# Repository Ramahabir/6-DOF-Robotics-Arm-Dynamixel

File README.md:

# STM32F411 6-DOF Robot Arm Controller

Firmware for a 6-degree-of-freedom robot arm based on an STM32F411CEU6 (Black Pill). The controller operates four Dynamixel joints over a half-duplex serial bus and provides PWM channels for the end effector.

The project uses STM32Cube HAL with PlatformIO and is uploaded through the USB-to-TTL serial adapter (upload protocol `serial`).

## System overview

- **4 × Dynamixel joints** — controlled through USART2 using Dynamixel Protocol 1.0
- **1 × wrist/gripper rotation servo** — PWM output on PA8 (TIM1_CH1, configured but not started)
- **1 × gripper servo** — PWM output on PA6 (TIM3_CH1)
- **USB-to-TTL data logger/telemetry** — connected through USART1 (PB6/PB7)
- **ESP32-C3 Super Mini** — planned wireless interface through USART6 (PA11/PA12)
- **74LS241 buffer** — converts the Dynamixel UART connection into a controlled half-duplex bus

## Hardware

- STM32F411CEU6 Black Pill development board
- Dynamixel AX-series actuators (the driver currently targets the AX-12A control table)
- 74LS241 tri-state buffer for the Dynamixel half-duplex bus
- Two PWM-compatible hobby servos
- USB-to-TTL serial adapter
- ESP32-C3 Super Mini (planned)
- Suitable external power supplies for the Dynamixel and hobby servos

## Controller PCB

The repository includes the editable KiCad source for the custom controller PCB. The board combines the STM32F411 Black Pill, ESP32-C3 Super Mini, 74LS241 Dynamixel interface, power input, actuator connectors, and development headers on one carrier board.

Open [`pcb/6dof.kicad_pro`](pcb/6dof.kicad_pro) in **KiCad 9.0 or newer** to view or modify the complete project.

### Schematic

Editable source: [`pcb/6dof.kicad_sch`](pcb/6dof.kicad_sch)

### PCB layout

Editable source: [`pcb/6dof.kicad_pcb`](pcb/6dof.kicad_pcb)

### 3D preview

> The KiCad files are active design sources. Review the schematic, complete the design-rule checks, and verify all footprints and routing before ordering a PCB. Gerber files, drill files, and a bill of materials are not included yet.

## Pin assignment

| Function | STM32 peripheral | Pin | Direction | Notes |
|---|---|---:|---|---|
| Dynamixel TX | USART2_TX | PA2 | Output | 1 Mbps, 8-N-1 |
| Dynamixel RX | USART2_RX | PA3 | Input | Receives Dynamixel status packets |
| 74LS241 direction | GPIO | PB0 | Output | High = transmit, low = receive/bus released |
| Data logger/telemetry TX | USART1_TX | PB6 | Output | 115200, 8-N-1; connect to USB-to-TTL RX |
| Data logger RX | USART1_RX | PB7 | Input | Connect to USB-to-TTL TX |
| ESP32-C3 TX | USART6_TX | PA11 | Output | 115200, 8-N-1; planned wireless link; connect to ESP32 RX |
| ESP32-C3 RX | USART6_RX | PA12 | Input | Planned wireless link; connect to ESP32 TX |
| Gripper rotation servo | TIM1_CH1 | PA8 | PWM output | Rotates the gripper (not started by default) |
| Gripper servo | TIM3_CH1 | PA6 | PWM output | Opens and closes the gripper |
| Built-in status LED | GPIO | PC13 | Output | Active-low on the Black Pill |

> The README pin table matches the generated firmware. If you target the earlier `PA9/PA10` USART1 design, update the alternate-function configuration in `src/usart.c` before wiring.

## Dynamixel bus

Dynamixel Protocol 1.0 uses a single bidirectional data wire. USART2 provides separate TX and RX signals, so the 74LS241 is used to control when the STM32 drives the bus.

```text
STM32 PA2 (USART2_TX) ──> 74LS241 input
STM32 PB0 (DIR)       ──> 74LS241 output-enable/direction control
74LS241 bus output    ──> Dynamixel DATA
STM32 PA3 (USART2_RX) <── Dynamixel DATA / receive path

STM32 GND ─────────────── Dynamixel interface GND
```

The firmware sets PB0 high while transmitting and returns it low before waiting for a servo response. USART2 is configured for **1,000,000 baud, 8 data bits, no parity, and 1 stop bit**.

Do not power the actuators from the STM32 board. Use correctly rated external supplies and connect the grounds of the STM32, servo supplies, Dynamixel bus, USB-to-TTL adapter, and ESP32 interface.

## Joint IDs

The current firmware polls the following joints. With torque off, move them by hand and verify the reported raw values change.

| Joint | Dynamixel ID | Notes |
|---|---:|---|
| Base | 1 | Home ≈ 512 |
| Shoulder | 9 | Home ≈ 315 |
| Elbow | 13 | Home ≈ 512 |
| Wrist | 3 | Home ≈ 512 |

For AX-series position control, raw values `0..1023` represent approximately `0..300°`:

```text
angle = raw_position × 300 / 1023
```

## Telemetry output

The firmware runs with **torque off** on all four joints. It reads present position, speed, load, voltage, temperature, and the moving flag for each joint, then prints one line to **both USART1 and USART6** (115200 baud, 8-N-1):

```text
BASE,826,0,0,124,32,IDL SHD,651,0,0,121,32,IDL ELB,557,0,0,124,32,IDL WRI,532,0,0,124,32,IDL
```

Each joint is separated by a space and contains comma-separated fields:

| Field | Meaning |
|---|---|
| `NAME` | Joint name (`BASE`, `SHD`, `ELB`, `WRI`) |
| `pos` | Present position, raw 0–1023 |
| `spd` | Present speed (0–1023); 0 = stationary |
| `load` | Present load, centered on 0 |
| `V` | Supply voltage in tenths of a volt (e.g. `124` = 12.4 V) |
| `T` | Servo board temperature in °C |
| `mov` | `IDL` = idle, `MOV` = rotating |

If a joint does not respond, that joint prints `NAME,ERROR,<code>` instead of numeric fields. On startup, USART1 also prints `Dynamixel ready (torque off)` once.

## Firmware status

Currently implemented:

- USART2 Dynamixel Protocol 1.0 communication at 1 Mbps, half-duplex direction control through PB0
- Ping, 8/16-bit read and write, torque, LED, goal-position, speed, present-position, present-speed, load, voltage, temperature, and moving-flag commands
- Packet validation for ID, length, checksum, timeout, and servo-reported errors
- Telemetry logging to USART1 (PB6/PB7) and USART6 (PA11/PA12) at 115200 baud
- Torque-off startup so joints can be moved by hand while powered
- TIM3 channel 1 PWM for PA6 (started); TIM1 channel 1 PWM for PA8 (configured, not started)

Still to be integrated into the active application:

- Enable torque and add coordinated motion control for the arm axes
- Start the TIM1 (PA8) gripper-rotation PWM channel
- Define the command protocol between the STM32 and ESP32-C3
- Optional data-fusion/feedback layer for closed-loop control

## Building and uploading

### Requirements

- [Visual Studio Code](https://code.visualstudio.com/) with the PlatformIO extension, or PlatformIO Core
- USB-to-TTL serial adapter
- External power supplies for the Dynamixel actuators

### PlatformIO commands

Build the firmware:

```sh
pio run
```

Upload over the serial adapter (the default `upload_protocol = serial` must match the connected adapter and bootloader):

```sh
pio run --target upload
```

Open the serial monitor on the USB-to-TTL adapter (e.g. `COM11`) for telemetry output:

```sh
pio device monitor --port COM11 --baud 115200
```

The PlatformIO environment is `genericSTM32F411CE`, using the STM32Cube framework and serial upload.

## Project structure

```text
.
├── include/
│   ├── dynamixel.h       # Dynamixel driver API and control-table addresses
│   ├── gpio.h
│   ├── main.h
│   ├── tim.h
│   └── usart.h
├── docs/
│   ├── 3dpcb.png         # Render of the assembled controller PCB
│   ├── pcb_footprint.png # PCB routing and footprint preview
│   ├── schematic.png     # Controller schematic preview
│   └── stm32pinout.png   # STM32 peripheral pin assignment
├── pcb/
│   ├── 6dof.kicad_pcb    # Editable PCB layout
│   ├── 6dof.kicad_pro    # KiCad project settings
│   └── 6dof.kicad_sch    # Editable schematic
├── src/
│   ├── dynamixel.c       # Protocol 1.0 packet transport and commands
│   ├── gpio.c            # LED and 74LS241 direction GPIO setup
│   ├── main.c            # Active test application
│   ├── tim.c             # PA8 and PA6 PWM timer configuration
│   └── usart.c           # USART1 and USART2 configuration
├── main_lama/            # Earlier application code kept for reference
└── platformio.ini        # PlatformIO target and build configuration
```

## Safety notes

- Test one actuator at a time before operating the complete arm.
- Verify Dynamixel IDs and baud rates before enabling torque.
- Keep the arm clear of people and objects during first motion tests.
- Use a current-limited actuator supply and provide an accessible emergency power cutoff.
- Set conservative position and speed limits in software to prevent mechanical collisions.
- Never connect 5 V logic directly to a non-5-V-tolerant STM32 input; verify the complete 74LS241 interface and supply arrangement before powering it.

## License

This project is open-source software available under the [MIT License](LICENSE).

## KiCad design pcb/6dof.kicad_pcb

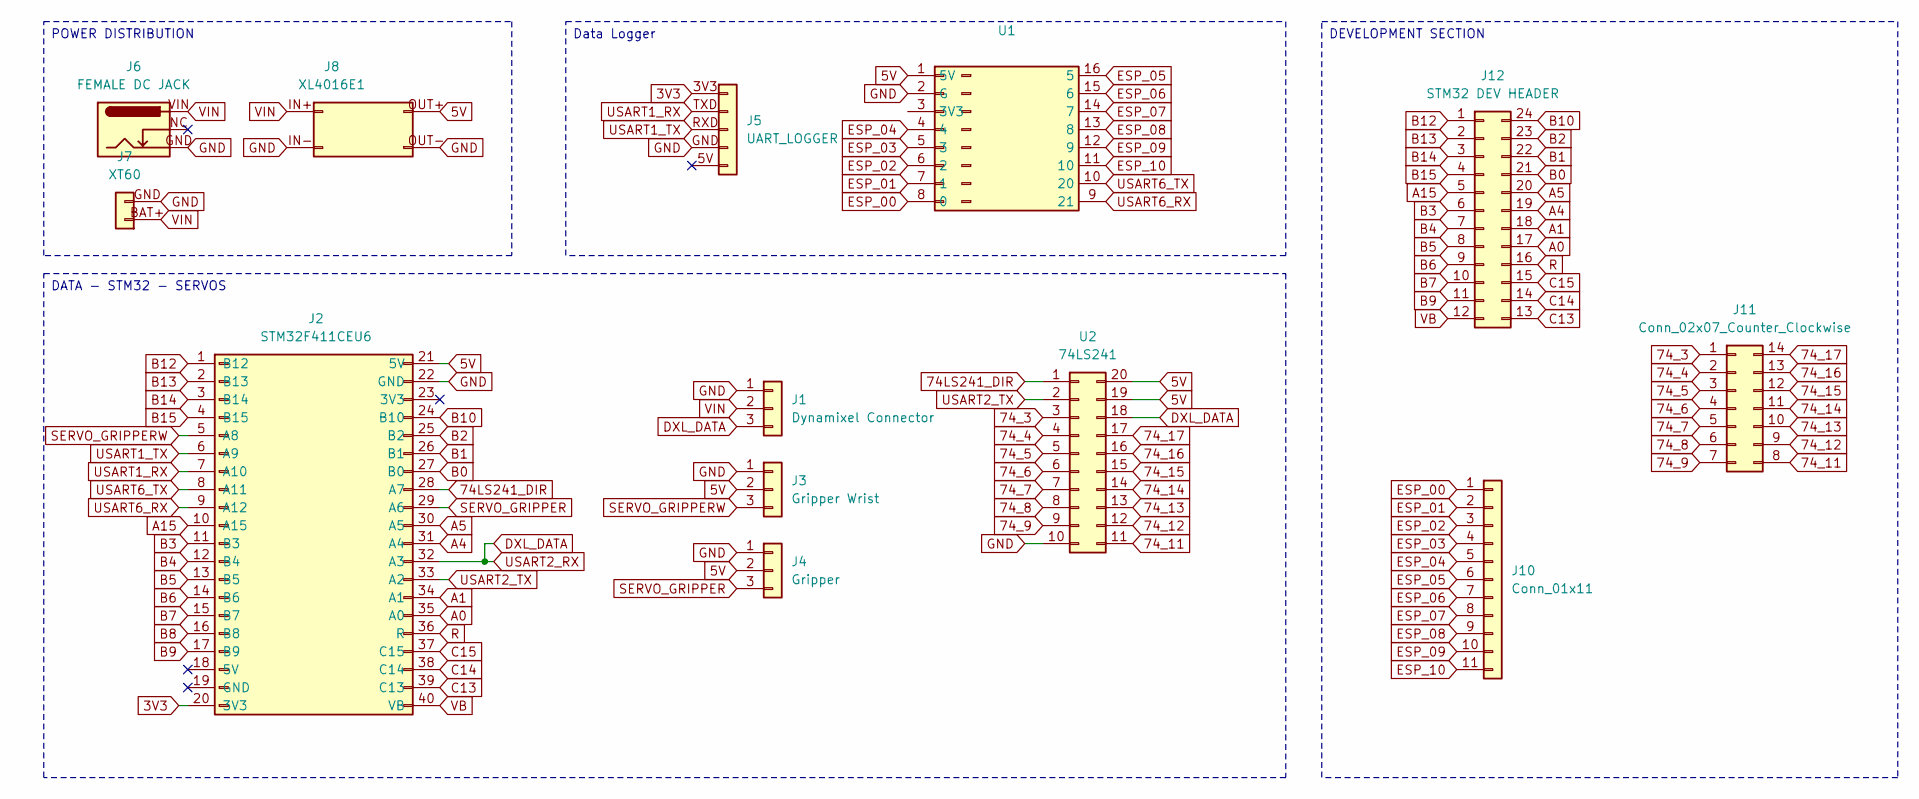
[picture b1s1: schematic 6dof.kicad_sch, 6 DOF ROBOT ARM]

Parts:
J1: Dynamixel Connector; Molex_KK-254_AE-6410-03A_1x03_P2.54mm_Vertical
J2: STM32F411CEU6
J3: Gripper Wrist; Molex_KK-254_AE-6410-03A_1x03_P2.54mm_Vertical
J4: Gripper; Molex_KK-254_AE-6410-03A_1x03_P2.54mm_Vertical
J5: UART_LOGGER; Molex_KK-254_AE-6410-05A_1x05_P2.54mm_Vertical
J6: FEMALE DC JACK; BarrelJack_CUI_PJ-102AH_Horizontal
J7: XT60; AMASS_XT60PW-M_1x02_P7.20mm_Horizontal
J8: XL4016E1
J10: Conn_01x11; PinHeader_1x11_P2.54mm_Vertical
J11: Conn_02x07_Counter_Clockwise; PinHeader_2x07_P2.54mm_Vertical
J12: STM32 DEV HEADER; PinHeader_2x12_P2.54mm_Vertical
U1: ESP32 C3 SUPERMINI
U2: 74LS241; DIP-20_W7.62mm

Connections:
3V3: J2.20 (3V3), J5.3V3
5V: J2.21 (5V), J3.2, J4.2, J8.OUT+ (Pin_4), U1.1 (5V), U2.19, U2.20
74LS241_DIR: J2.28 (A7), U2.1
74_3: J11.1, U2.3
74_4: J11.2, U2.4
74_5: J11.3, U2.5
74_6: J11.4, U2.6
74_7: J11.5, U2.7
74_8: J11.6, U2.8
74_9: J11.7, U2.9
74_11: J11.8, U2.11
74_12: J11.9, U2.12
74_13: J11.10, U2.13
74_14: J11.11, U2.14
74_15: J11.12, U2.15
74_16: J11.13, U2.16
74_17: J11.14, U2.17
A0: J2.35 (A0), J12.17
A1: J2.34 (A1), J12.18
A4: J2.31 (A4), J12.19
A5: J2.30 (A5), J12.20
A15: J2.10 (A15), J12.5
B0: J2.27 (B0), J12.21
B1: J2.26 (B1), J12.22
B2: J2.25 (B2), J12.23
B3: J2.11 (B3), J12.6
B4: J2.12 (B4), J12.7
B5: J2.13 (B5), J12.8
B6: J2.14 (B6), J12.9
B7: J2.15 (B7), J12.10
B8: J2.16 (B8)
B9: J2.17 (B9), J12.11
B10: J2.24 (B10), J12.24
B12: J2.1 (B12), J12.1
B13: J2.2 (B13), J12.2
B14: J2.3 (B14), J12.3
B15: J2.4 (B15), J12.4
C13: J2.39 (C13), J12.13
C14: J2.38 (C14), J12.14
C15: J2.37 (C15), J12.15
DXL_DATA: J1.3, J2.32 (A3), U2.18
ESP_00: J10.1, U1.8 (0)
ESP_01: J10.2, U1.7 (1)
ESP_02: J10.3, U1.6 (2)
ESP_03: J10.4, U1.5 (3)
ESP_04: J10.5, U1.4
ESP_05: J10.6, U1.16 (5)
ESP_06: J10.7, U1.15 (6)
ESP_07: J10.8, U1.14 (7)
ESP_08: J10.9, U1.13 (8)
ESP_09: J10.10, U1.12 (9)
ESP_10: J10.11, U1.11 (10)
GND: J1.1, J2.22 (GND), J3.1, J4.1, J5.GND, J6.GND, J7.GND (Pin_2), J8.IN- (Pin_2), J8.OUT- (Pin_3), U1.2 (G), U2.10
R: J2.36 (R), J12.16
SERVO_GRIPPER: J2.29 (A6), J4.3
SERVO_GRIPPERW: J2.5 (A8), J3.3
USART1_RX: J2.7 (A10), J5.TXD
USART1_TX: J2.6 (A9), J5.RXD
USART2_TX: J2.33 (A2), U2.2
USART6_RX: J2.9 (A12), U1.9 (21)
USART6_TX: J2.8 (A11), U1.10 (20)
VB: J2.40 (VB), J12.12
VIN: J1.2, J6.VIN, J7.BAT+ (Pin_1), J8.IN+ (Pin_1)

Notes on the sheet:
DATA - STM32 - SERVOS
DEVELOPMENT SECTION
Data Logger
POWER DISTRIBUTION

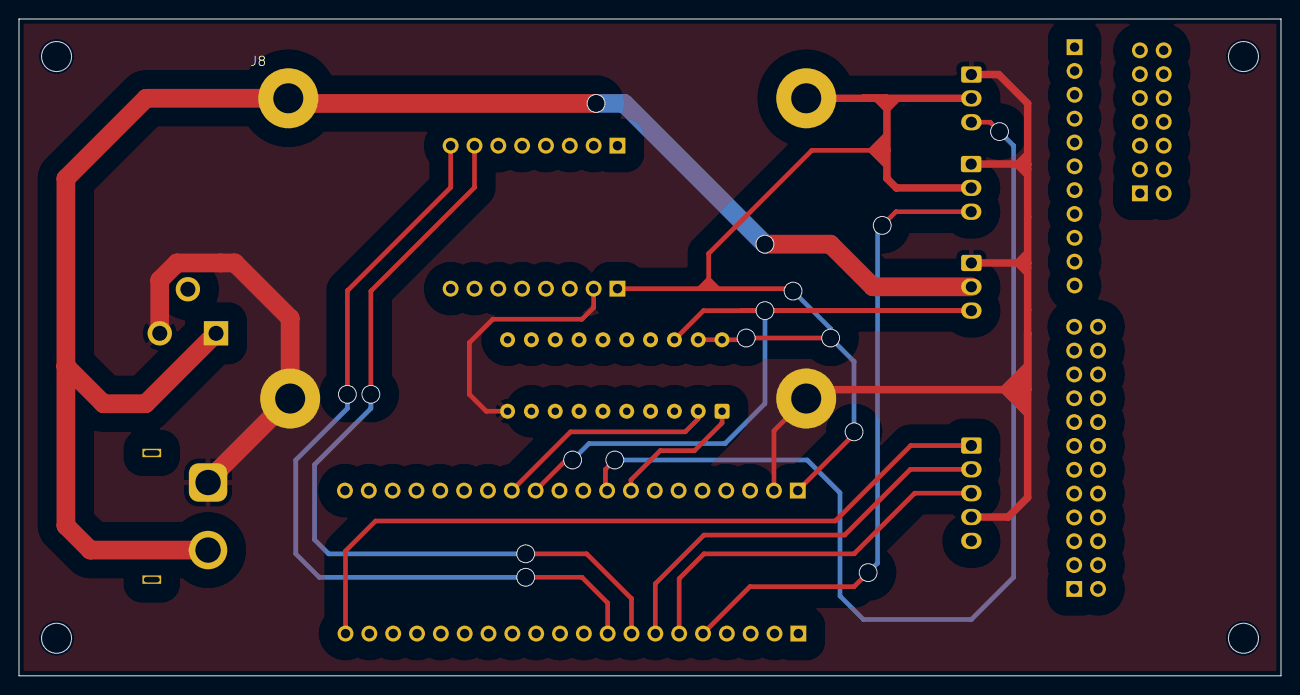
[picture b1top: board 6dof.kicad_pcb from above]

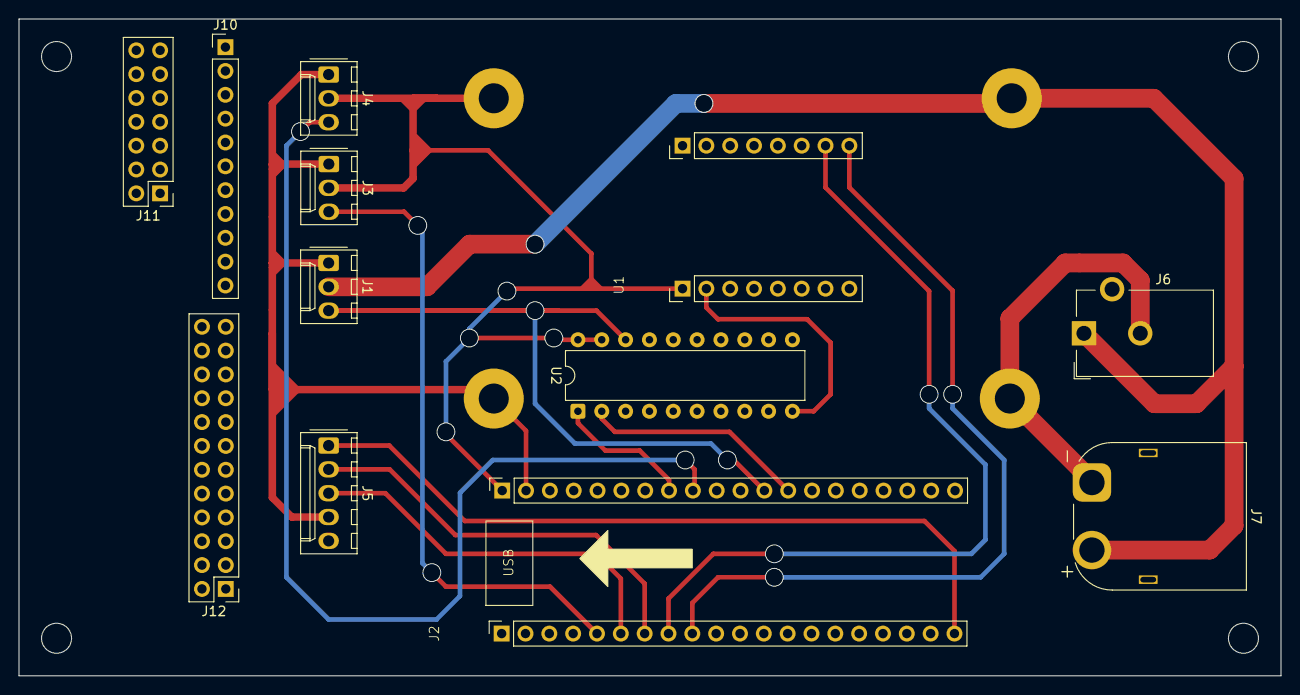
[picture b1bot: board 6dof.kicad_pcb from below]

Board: 2 copper layers, 134.5 x 70.0 mm, 13 parts (12 on the bottom side), 62 nets.

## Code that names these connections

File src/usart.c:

/* USER CODE BEGIN Header */
/**
  ******************************************************************************
  * @file    usart.c
  * @brief   This file provides code for the configuration
  *          of the USART instances.
  ******************************************************************************
  * @attention
  *
  * Copyright (c) 2026 STMicroelectronics.
  * All rights reserved.
  *
  * This software is licensed under terms that can be found in the LICENSE file
  * in the root directory of this software component.
  * If no LICENSE file comes with this software, it is provided AS-IS.
  *
  ******************************************************************************
  */
/* USER CODE END Header */
/* Includes ------------------------------------------------------------------*/
#include "usart.h"

/* USER CODE BEGIN 0 */

/* USER CODE END 0 */

UART_HandleTypeDef huart1;
UART_HandleTypeDef huart2;
UART_HandleTypeDef huart6;

/* USART1 init function */

void MX_USART1_UART_Init(void)
{

  /* USER CODE BEGIN USART1_Init 0 */

  /* USER CODE END USART1_Init 0 */

  /* USER CODE BEGIN USART1_Init 1 */

  /* USER CODE END USART1_Init 1 */
  huart1.Instance = USART1;
  huart1.Init.BaudRate = 115200;
  huart1.Init.WordLength = UART_WORDLENGTH_8B;
  huart1.Init.StopBits = UART_STOPBITS_1;
  huart1.Init.Parity = UART_PARITY_NONE;
  huart1.Init.Mode = UART_MODE_TX_RX;
  huart1.Init.HwFlowCtl = UART_HWCONTROL_NONE;
  huart1.Init.OverSampling = UART_OVERSAMPLING_16;
  if (HAL_UART_Init(&huart1) != HAL_OK)
  {
    Error_Handler();
  }
  /* USER CODE BEGIN USART1_Init 2 */

  /* USER CODE END USART1_Init 2 */

}
/* USART2 init function */

void MX_USART2_UART_Init(void)
{

  /* USER CODE BEGIN USART2_Init 0 */

  /* USER CODE END USART2_Init 0 */

  /* USER CODE BEGIN USART2_Init 1 */

  /* USER CODE END USART2_Init 1 */
  huart2.Instance = USART2;
  /* AX-series factory-default bus speed. */
  huart2.Init.BaudRate = 1000000;
  huart2.Init.WordLength = UART_WORDLENGTH_8B;
  huart2.Init.StopBits = UART_STOPBITS_1;
  huart2.Init.Parity = UART_PARITY_NONE;
  huart2.Init.Mode = UART_MODE_TX_RX;
  huart2.Init.HwFlowCtl = UART_HWCONTROL_NONE;
  huart2.Init.OverSampling = UART_OVERSAMPLING_16;
  if (HAL_UART_Init(&huart2) != HAL_OK)
  {
    Error_Handler();
  }
  /* USER CODE BEGIN USART2_Init 2 */

  /* USER CODE END USART2_Init 2 */

}

/* USART6 init function */

void MX_USART6_UART_Init(void)
{
  huart6.Instance = USART6;
  huart6.Init.BaudRate = 115200;
  huart6.Init.WordLength = UART_WORDLENGTH_8B;
  huart6.Init.StopBits = UART_STOPBITS_1;
  huart6.Init.Parity = UART_PARITY_NONE;
  huart6.Init.Mode = UART_MODE_TX_RX;
  huart6.Init.HwFlowCtl = UART_HWCONTROL_NONE;
  huart6.Init.OverSampling = UART_OVERSAMPLING_16;
  if (HAL_UART_Init(&huart6) != HAL_OK)
  {
    Error_Handler();
  }
}

void HAL_UART_MspInit(UART_HandleTypeDef* uartHandle)
{

  GPIO_InitTypeDef GPIO_InitStruct = {0};
  if(uartHandle->Instance==USART1)
  {
  /* USER CODE BEGIN USART1_MspInit 0 */

  /* USER CODE END USART1_MspInit 0 */
    /* USART1 clock enable */
    __HAL_RCC_USART1_CLK_ENABLE();

    __HAL_RCC_GPIOB_CLK_ENABLE();
    /**USART1 GPIO Configuration
    PB6     ------> USART1_TX
    PB7     ------> USART1_RX
    */
    GPIO_InitStruct.Pin = GPIO_PIN_6|GPIO_PIN_7;
    GPIO_InitStruct.Mode = GPIO_MODE_AF_PP;
    GPIO_InitStruct.Pull = GPIO_NOPULL;
    GPIO_InitStruct.Speed = GPIO_SPEED_FREQ_VERY_HIGH;
    GPIO_InitStruct.Alternate = GPIO_AF7_USART1;
    HAL_GPIO_Init(GPIOB, &GPIO_InitStruct);

  /* USER CODE BEGIN USART1_MspInit 1 */

  /* USER CODE END USART1_MspInit 1 */
  }
  else if(uartHandle->Instance==USART2)
  {
  /* USER CODE BEGIN USART2_MspInit 0 */

  /* USER CODE END USART2_MspInit 0 */
    /* USART2 clock enable */
    __HAL_RCC_USART2_CLK_ENABLE();

    __HAL_RCC_GPIOA_CLK_ENABLE();
    /**USART2 GPIO Configuration
    PA2     ------> USART2_TX
    PA3     ------> USART2_RX
    */
    GPIO_InitStruct.Pin = GPIO_PIN_2|GPIO_PIN_3;
    GPIO_InitStruct.Mode = GPIO_MODE_AF_PP;
    GPIO_InitStruct.Pull = GPIO_NOPULL;
    GPIO_InitStruct.Speed = GPIO_SPEED_FREQ_VERY_HIGH;
    GPIO_InitStruct.Alternate = GPIO_AF7_USART2;
    HAL_GPIO_Init(GPIOA, &GPIO_InitStruct);

  /* USER CODE BEGIN USART2_MspInit 1 */

  /* USER CODE END USART2_MspInit 1 */
  }
  else if(uartHandle->Instance==USART6)
  {
    /* USART6 clock enable */
    __HAL_RCC_USART6_CLK_ENABLE();

    __HAL_RCC_GPIOA_CLK_ENABLE();
    /**USART6 GPIO Configuration
    PA11     ------> USART6_TX
    PA12     ------> USART6_RX
    */
    GPIO_InitStruct.Pin = GPIO_PIN_11|GPIO_PIN_12;
    GPIO_InitStruct.Mode = GPIO_MODE_AF_PP;
    GPIO_InitStruct.Pull = GPIO_NOPULL;
    GPIO_InitStruct.Speed = GPIO_SPEED_FREQ_VERY_HIGH;
    GPIO_InitStruct.Alternate = GPIO_AF8_USART6;
    HAL_GPIO_Init(GPIOA, &GPIO_InitStruct);
  }
}

void HAL_UART_MspDeInit(UART_HandleTypeDef* uartHandle)
{

  if(uartHandle->Instance==USART1)
  {
  /* USER CODE BEGIN USART1_MspDeInit 0 */

  /* USER CODE END USART1_MspDeInit 0 */
    /* Peripheral clock disable */
    __HAL_RCC_USART1_CLK_DISABLE();

    /**USART1 GPIO Configuration
    PB6     ------> USART1_TX
    PB7     ------> USART1_RX
    */
    HAL_GPIO_DeInit(GPIOB, GPIO_PIN_6|GPIO_PIN_7);

  /* USER CODE BEGIN USART1_MspDeInit 1 */

  /* USER CODE END USART1_MspDeInit 1 */
  }
  else if(uartHandle->Instance==USART2)
  {
  /* USER CODE BEGIN USART2_MspDeInit 0 */

  /* USER CODE END USART2_MspDeInit 0 */
    /* Peripheral clock disable */
    __HAL_RCC_USART2_CLK_DISABLE();

    /**USART2 GPIO Configuration
    PA2     ------> USART2_TX
    PA3     ------> USART2_RX
    */
    HAL_GPIO_DeInit(GPIOA, GPIO_PIN_2|GPIO_PIN_3);

  /* USER CODE BEGIN USART2_MspDeInit 1 */

  /* USER CODE END USART2_MspDeInit 1 */
  }
  else if(uartHandle->Instance==USART6)
  {
    /* Peripheral clock disable */
    __HAL_RCC_USART6_CLK_DISABLE();

    /**USART6 GPIO Configuration
    PA11     ------> USART6_TX
    PA12     ------> USART6_RX
    */
    HAL_GPIO_DeInit(GPIOA, GPIO_PIN_11|GPIO_PIN_12);
  }
}

/* USER CODE BEGIN 1 */

/* USER CODE END 1 */
